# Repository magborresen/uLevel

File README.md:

# uLevel

The project is currently on hold since I sold my HyperCube and bought an Ender-3 instead. I might pick it back up at some point.

The µLevel a PCB strain gauge for 3D printer bed leveling.

It was originally designed for the HyperCube 3D printer, but is supposed to be able to mount on other printers. It is mounted on to of the hotend assembly with the filament/PTFE tube going through the middle of the pcb. This should ensure even pressure from the hotend assembly onto the PCB. 

The basic design is using the smallest traces that JLC PCB offers of 0.127mm to create as long traces as possible to create the resistance. This on done on both sides of the PCB.
This makes the circuit into a wheatstone bridge together with 2 non-variable resistors that can be an arbitrary value between 1k and 10k ohm. 

You can read more about the project here https://magnusborresen.com/index.php/2021/05/27/13103/

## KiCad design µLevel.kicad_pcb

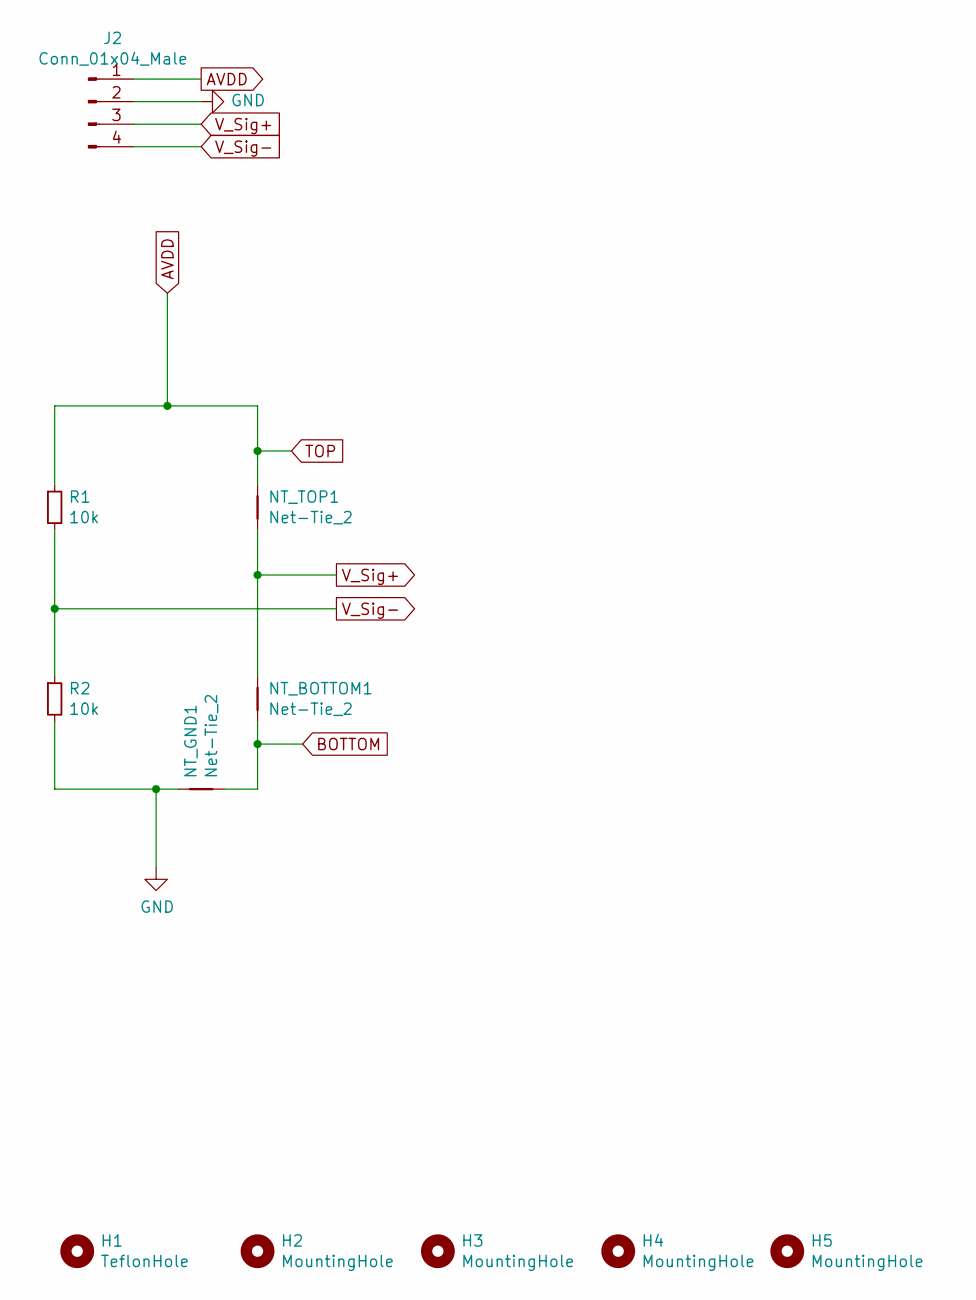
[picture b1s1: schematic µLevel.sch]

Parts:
H1: TeflonHole; Teflon_Mounting_Hole
H2, H3, H4, H5: MountingHole; MountingHole_2.2mm_M2_Pad
J2: Conn_01x04_Male; PinHeader_1x04_P2.54mm_Vertical
NT_BOTTOM1: Net-Tie_2; NetTie-2_SMD_Pad0.127mm
NT_GND1: Net-Tie_2; NetTie-2_SMD_Pad0.127mm
NT_TOP1: Net-Tie_2; NetTie-2_SMD_Pad0.127mm
R1, R2: 10k; R_0805_2012Metric_Pad1.15x1.40mm_HandSolder

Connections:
AVDD: J2.1, NT_TOP1.1, R1.1
BOTTOM: NT_BOTTOM1.2, NT_GND1.2
GND: J2.2, NT_GND1.1, R2.2
V_Sig+: J2.3, NT_BOTTOM1.1, NT_TOP1.2
V_Sig-: J2.4, R1.2, R2.1

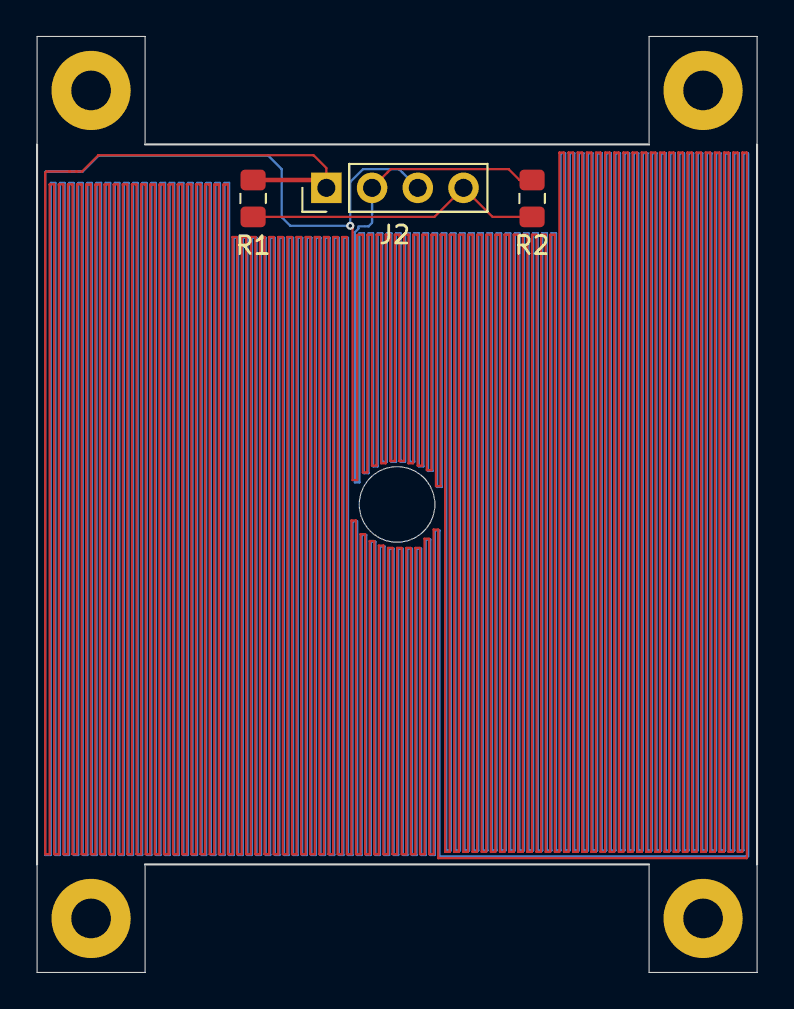
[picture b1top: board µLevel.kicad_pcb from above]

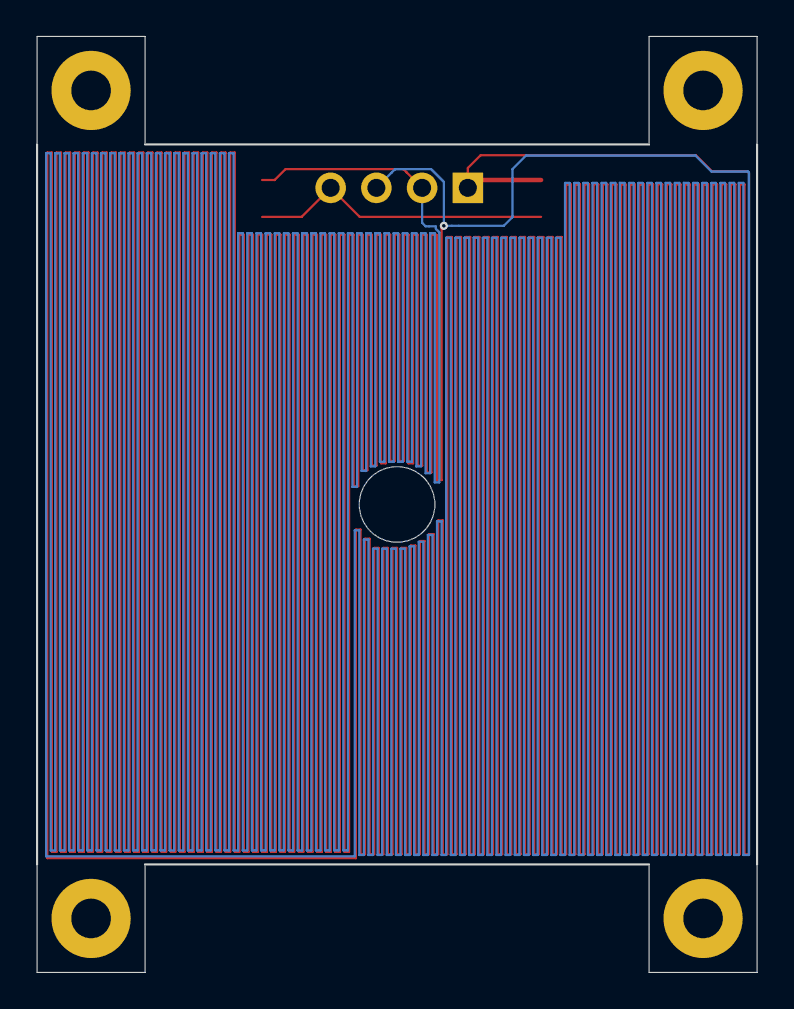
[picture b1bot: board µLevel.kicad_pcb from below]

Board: 2 copper layers, 40.0 x 51.9 mm, 11 parts (2 on the bottom side), 5 nets.

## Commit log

2020-10-16 initial commit of µlevel V1
